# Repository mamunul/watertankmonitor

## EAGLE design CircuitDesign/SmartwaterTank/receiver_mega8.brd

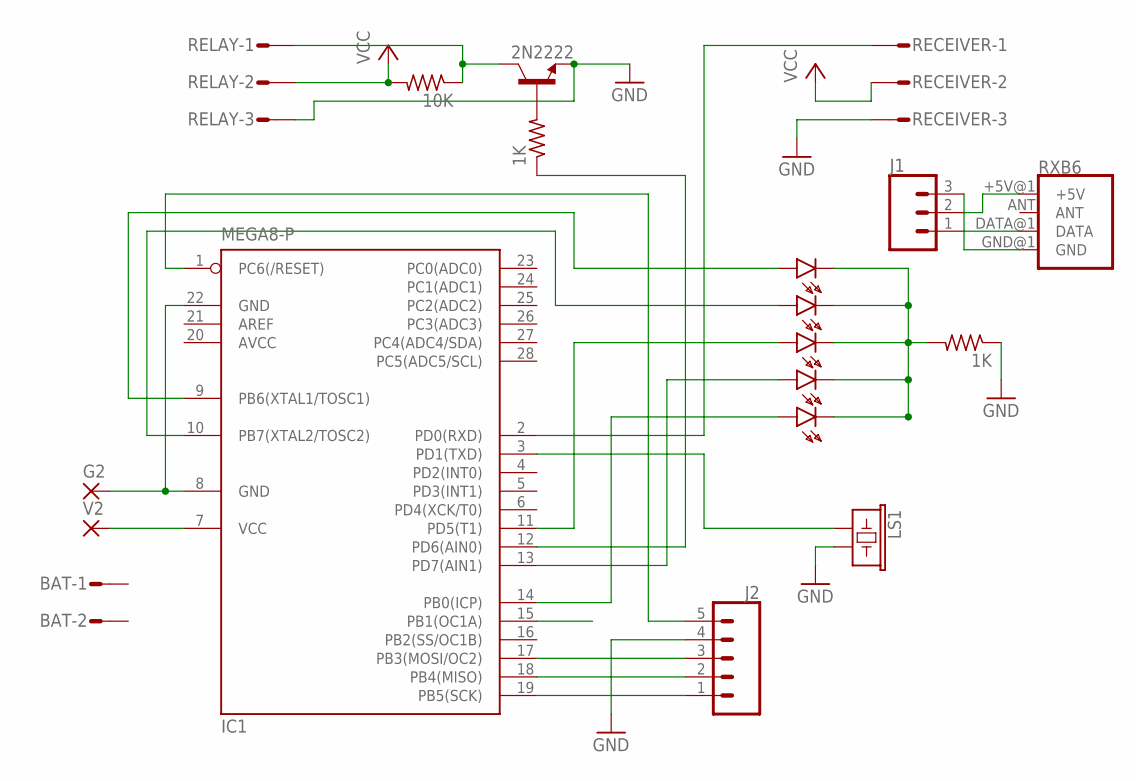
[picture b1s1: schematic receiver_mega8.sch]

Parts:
BAT: S02P
D2, D3, D4, D5, D6: HLMP6
G2: 1,6/0,8
IC1: MEGA8-P; DIL28-3
J1: CONN_03; 1X03
J2: CONN_05; 1X05
LS1: BUZZER-PTH_KIT; BUZZER-12MM-KIT
R1, R2: 1K; 0207/12
R5: 10K; 0207/12
RECEIVER: S03P
RELAY: S03P
RXB6: RF-LINK_RX
T1: 2N2222; TO92-CBE
V2: 1,6/0,8

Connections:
AVCC: IC1.20 (AVCC)
GND: J2.4, LS1.- (2), R2.1, RECEIVER.3, RELAY.3, T1.E
unnamed: R1.2, T1.B
unnamed: IC1.12 (PD6(AIN0)), R1.1
unnamed: J1.1, RXB6.DATA@1 (DATA)
unnamed: IC1.2 (PD0(RXD)), RECEIVER.1
unnamed: IC1.3 (PD1(TXD)), LS1.+ (1)
unnamed: D2.K, D3.K, D4.K, D5.K, D6.K, R2.2
unnamed: G2.1, IC1.8 (GND), IC1.22 (GND)
unnamed: IC1.7 (VCC), V2.1
unnamed: J1.3, RXB6.GND@1 (GND)
unnamed: D6.A, IC1.9 (PB6(XTAL1/TOSC1))
unnamed: D5.A, IC1.10 (PB7(XTAL2/TOSC2))
unnamed: D4.A, IC1.11 (PD5(T1))
unnamed: D3.A, IC1.13 (PD7(AIN1))
unnamed: J1.2, RXB6.+5V@1 (+5V)
unnamed: D2.A, IC1.14 (PB0(ICP))
unnamed: R5.1, RELAY.1, T1.C
unnamed: IC1.19 (PB5(SCK)), J2.1
unnamed: IC1.18 (PB4(MISO)), J2.2
unnamed: IC1.17 (PB3(MOSI/OC2)), J2.3
unnamed: IC1.1 (PC6(/RESET)), J2.5
VCC: R5.2, RECEIVER.2, RELAY.2

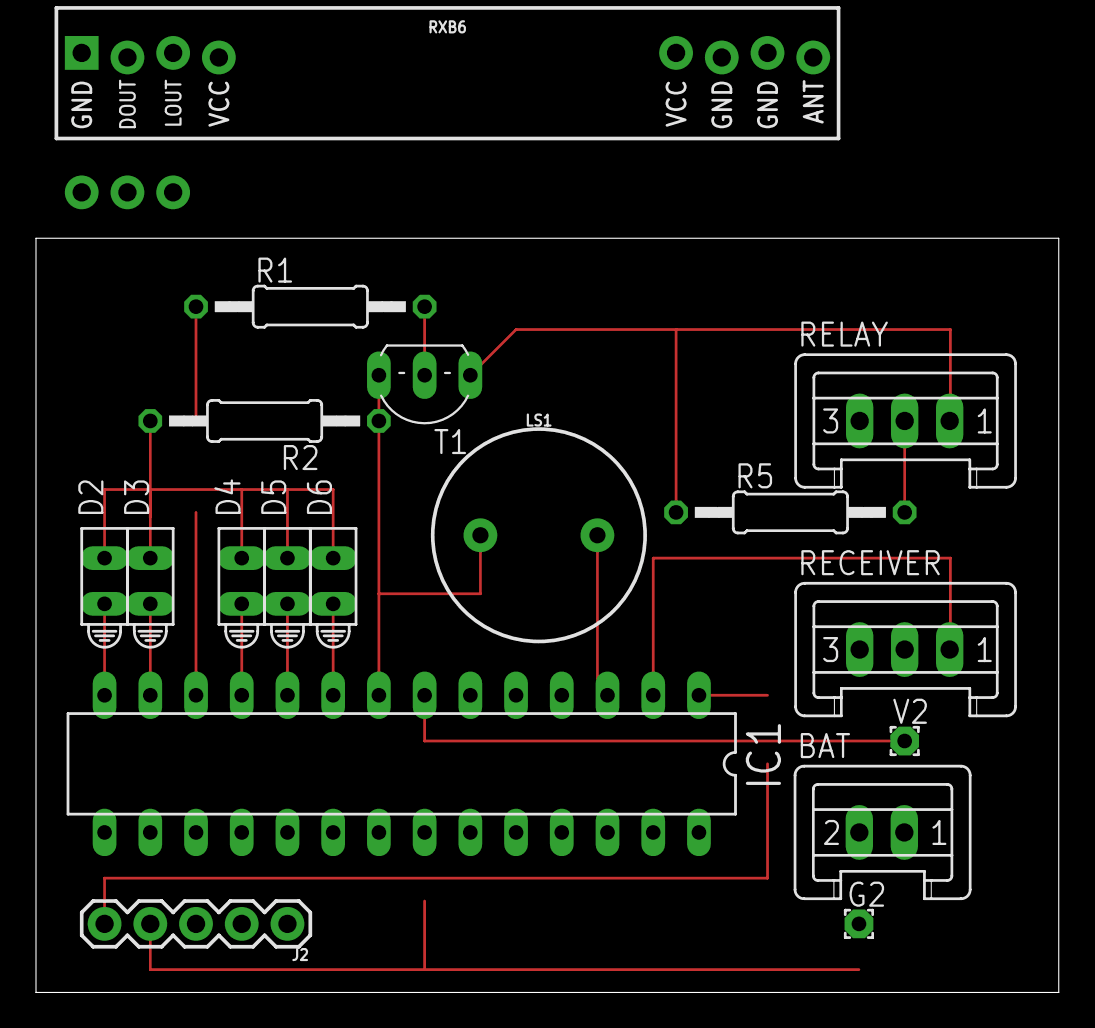
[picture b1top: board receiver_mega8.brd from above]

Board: 2 copper layers, 56.8 x 41.9 mm, 19 parts (1 on the bottom side), 22 nets.

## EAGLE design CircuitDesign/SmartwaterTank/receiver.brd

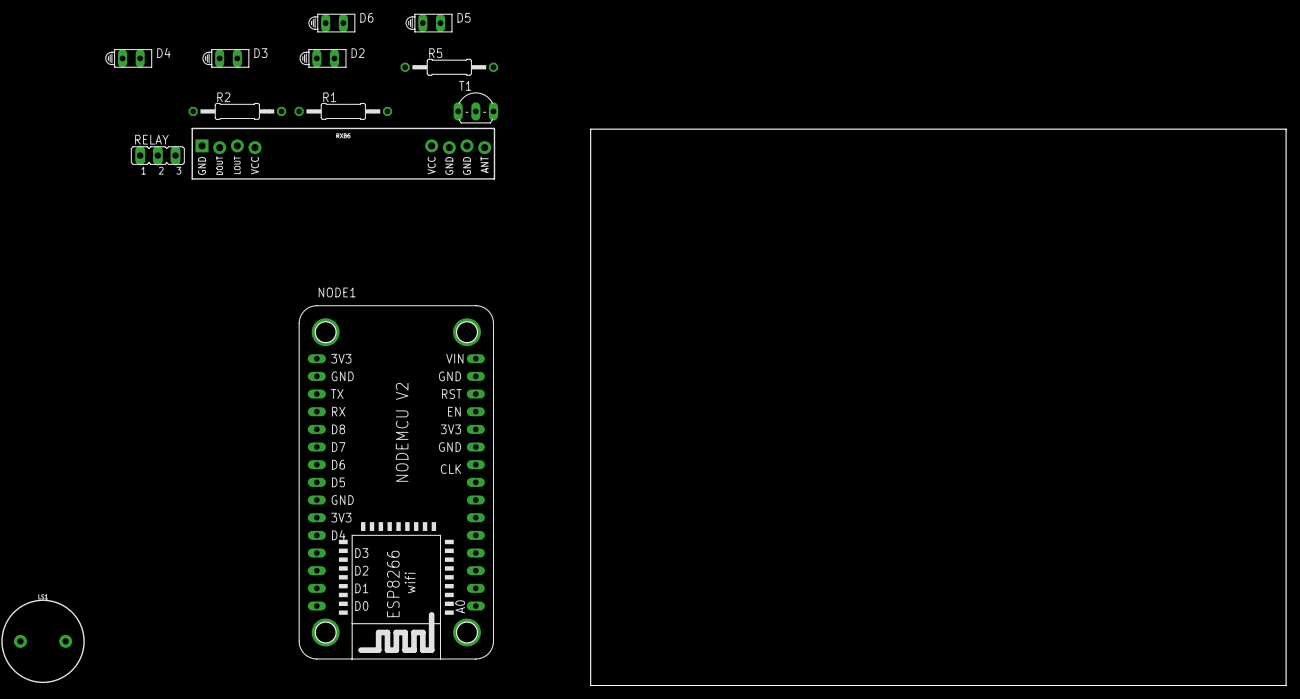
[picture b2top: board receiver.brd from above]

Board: 2 copper layers, 100.0 x 80.0 mm, 13 parts (0 on the bottom side), 14 nets, no tracks yet.

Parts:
D2, D3, D4, D5, D6: HLMP6
LS1: BUZZER-PTH_KIT; BUZZER-12MM-KIT
NODE1: NODEMCU_ESP8266
R1, R2: 1K; 0207/12
R5: 10K; 0207/12
RELAY: JP2
RXB6: RF-LINK_RX
T1: 2N2222; TO92-CBE

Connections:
3V3: NODE1.3V3@1, NODE1.3V3@2, NODE1.3V3@3
GND: LS1.-, NODE1.GND@1, NODE1.GND@2, NODE1.GND@3, NODE1.GND@4, R2.1, RELAY.3, RXB6.GND@1, T1.E
unnamed: R1.2, T1.B
unnamed: NODE1.D0, R1.1
unnamed: R5.1, RELAY.2, T1.C
unnamed: NODE1.D4, RXB6.DATA@1
unnamed: LS1.+, NODE1.D1
unnamed: D2.K, D3.K, D4.K, D5.K, D6.K, R2.2
unnamed: D6.A, NODE1.D8
unnamed: D5.A, NODE1.D7
unnamed: D4.A, NODE1.D6
unnamed: D3.A, NODE1.D5
unnamed: D2.A, NODE1.D3
VCC: R5.2, RELAY.1, RXB6.+5V@1

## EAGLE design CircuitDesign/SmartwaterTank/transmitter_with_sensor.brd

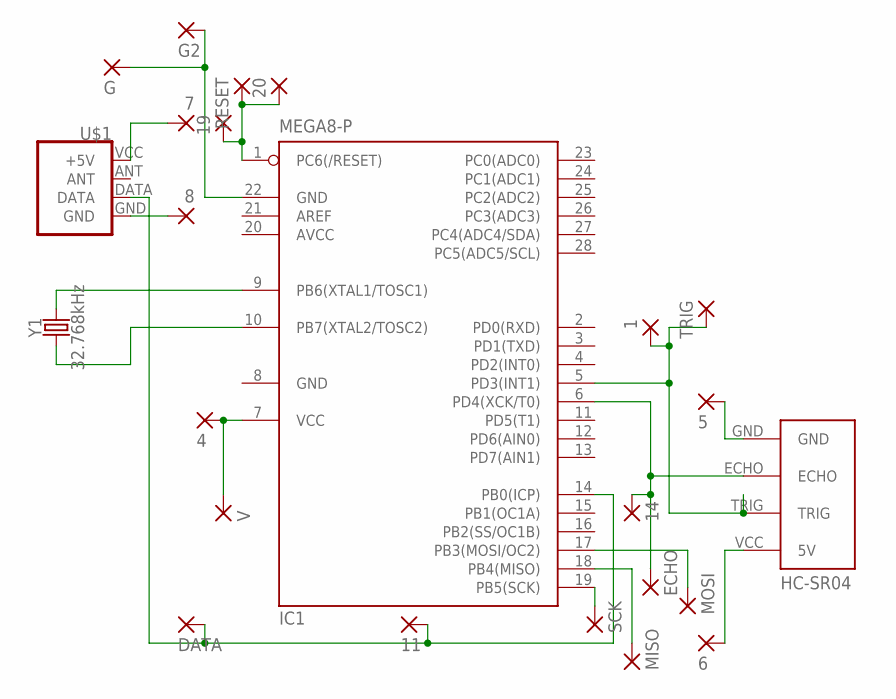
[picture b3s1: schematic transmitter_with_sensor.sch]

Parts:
1, 4, 5, 6, 7, 8, 11, 14, 19, 20: WIREPAD1,6/0,8; 1,6/0,8
DATA: WIREPAD1,6/0,8; 1,6/0,8
ECHO: WIREPAD1,6/0,8; 1,6/0,8
G, G2: WIREPAD1,6/0,8; 1,6/0,8
IC1: MEGA8-P; DIL28-3
J_ULTRASONIC_1: HC-SR04; HC-SR04_FOOTPRINT
MISO: WIREPAD1,6/0,8; 1,6/0,8
MOSI: WIREPAD1,6/0,8; 1,6/0,8
RESET: WIREPAD1,6/0,8; 1,6/0,8
SCK: WIREPAD1,6/0,8; 1,6/0,8
TRIG: WIREPAD1,6/0,8; 1,6/0,8
U$1: RF-LINK_TX
V: WIREPAD1,6/0,8; 1,6/0,8
Y1: 32.768kHz; CRYSTAL-PTH-2X6-CYL

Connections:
AVCC: IC1.20 (AVCC)
GND: IC1.8 (GND)
unnamed: 6.1, J_ULTRASONIC_1.VCC (5V)
unnamed: G.1, G2.1, IC1.22 (GND)
unnamed: 4.1, IC1.7 (VCC), V.1
unnamed: 5.1, J_ULTRASONIC_1.GND
unnamed: 8.1, U$1.GND
unnamed: 7.1, U$1.VCC (+5V)
unnamed: IC1.9 (PB6(XTAL1/TOSC1)), Y1.2
unnamed: IC1.10 (PB7(XTAL2/TOSC2)), Y1.1
unnamed: 19.1, 20.1, IC1.1 (PC6(/RESET)), RESET.1
unnamed: 14.1, ECHO.1, IC1.6 (PD4(XCK/T0)), J_ULTRASONIC_1.ECHO
unnamed: 1.1, IC1.5 (PD3(INT1)), J_ULTRASONIC_1.TRIG, TRIG.1
unnamed: IC1.17 (PB3(MOSI/OC2)), MOSI.1
unnamed: IC1.18 (PB4(MISO)), MISO.1
unnamed: 11.1, DATA.1, IC1.14 (PB0(ICP)), U$1.DATA
unnamed: IC1.19 (PB5(SCK)), SCK.1

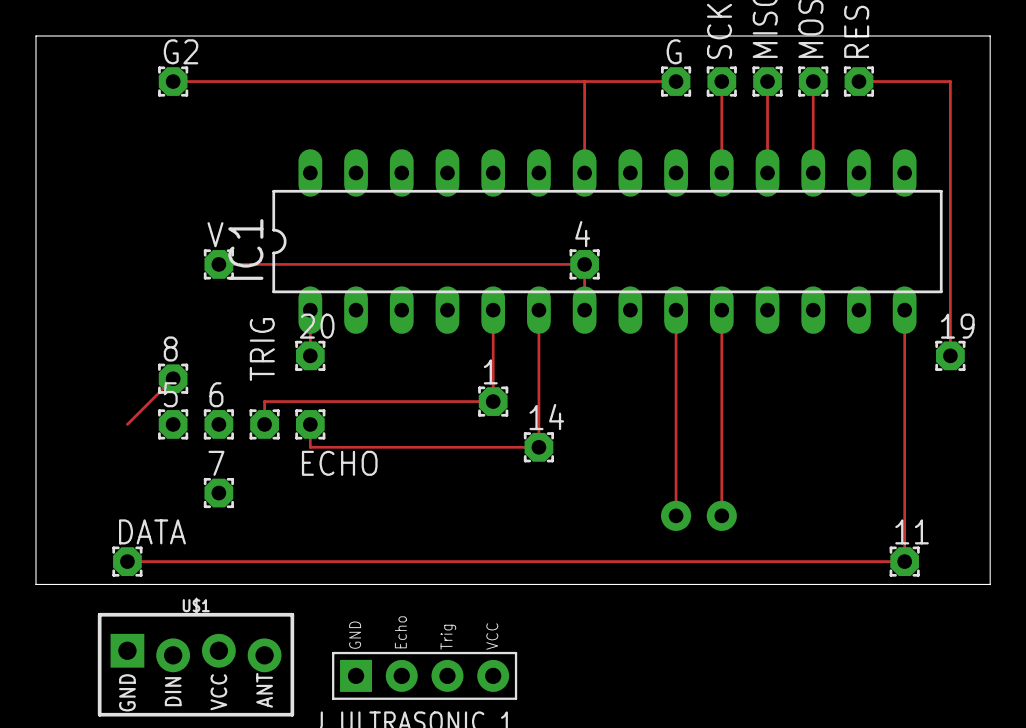
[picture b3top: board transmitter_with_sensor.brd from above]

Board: 2 copper layers, 53.0 x 30.5 mm, 24 parts (1 on the bottom side), 15 nets.

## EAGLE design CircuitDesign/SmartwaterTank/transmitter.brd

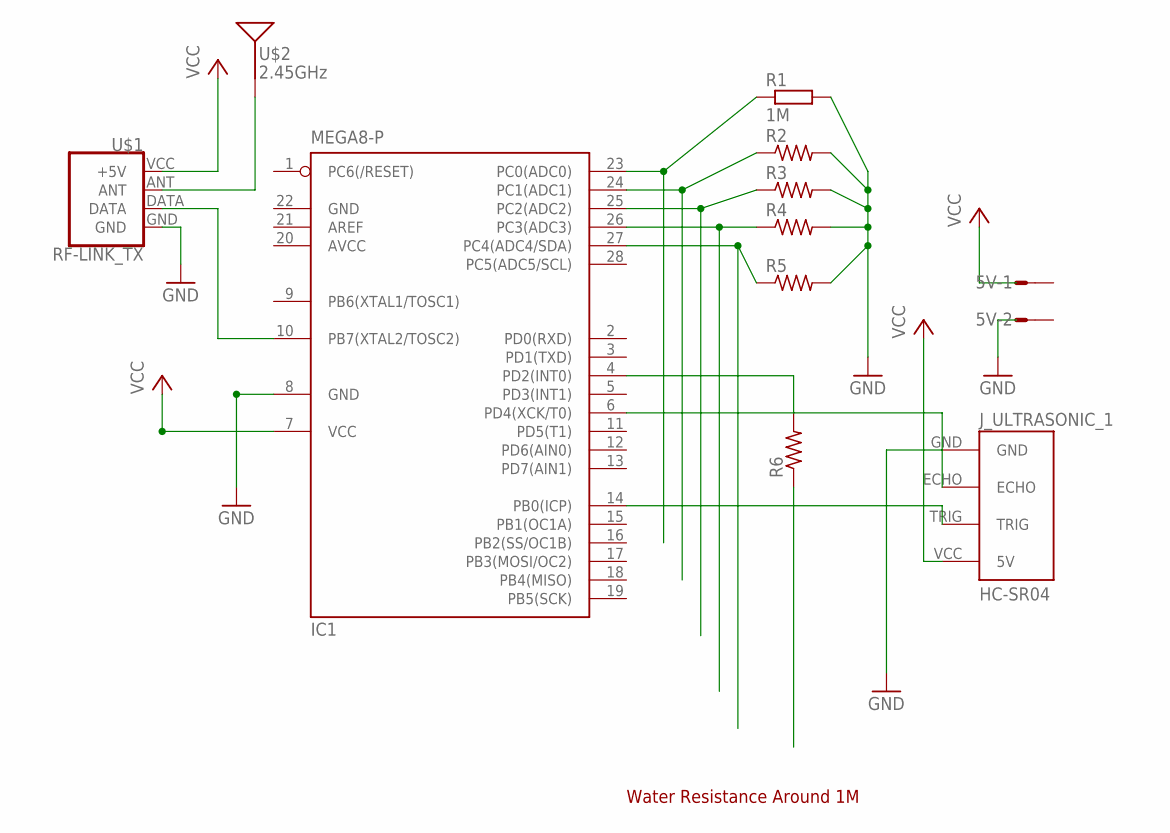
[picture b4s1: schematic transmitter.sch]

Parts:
5V: S02P
IC1: MEGA8-P; DIL28-3
J_ULTRASONIC_1: HC-SR04; HC-SR04_FOOTPRINT
R1: 1M; 0204/7
R2, R3, R4, R5, R6: R-US_0204/2V; 0204V
U$1: RF-LINK_TX
U$2: 2.45GHz; ANT-2.4GHZ-6.5X2.2MM

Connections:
AVCC: IC1.20 (AVCC)
GND: IC1.8 (GND), IC1.22 (GND), J_ULTRASONIC_1.GND, R1.2, R2.2, R3.2, R4.2, R5.2, U$1.GND
unnamed: IC1.23 (PC0(ADC0)), R1.1
unnamed: IC1.26 (PC3(ADC3)), R4.1
unnamed: IC1.25 (PC2(ADC2)), R3.1
unnamed: IC1.24 (PC1(ADC1)), R2.1
unnamed: IC1.27 (PC4(ADC4/SDA)), R5.1
unnamed: IC1.10 (PB7(XTAL2/TOSC2)), U$1.DATA
unnamed: U$1.ANT, U$2.FEED
unnamed: IC1.4 (PD2(INT0)), R6.2
unnamed: IC1.6 (PD4(XCK/T0)), J_ULTRASONIC_1.ECHO
unnamed: IC1.14 (PB0(ICP)), J_ULTRASONIC_1.TRIG
VCC: IC1.7 (VCC), J_ULTRASONIC_1.VCC (5V), U$1.VCC (+5V)

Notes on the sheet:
Water Resistance Around 1M

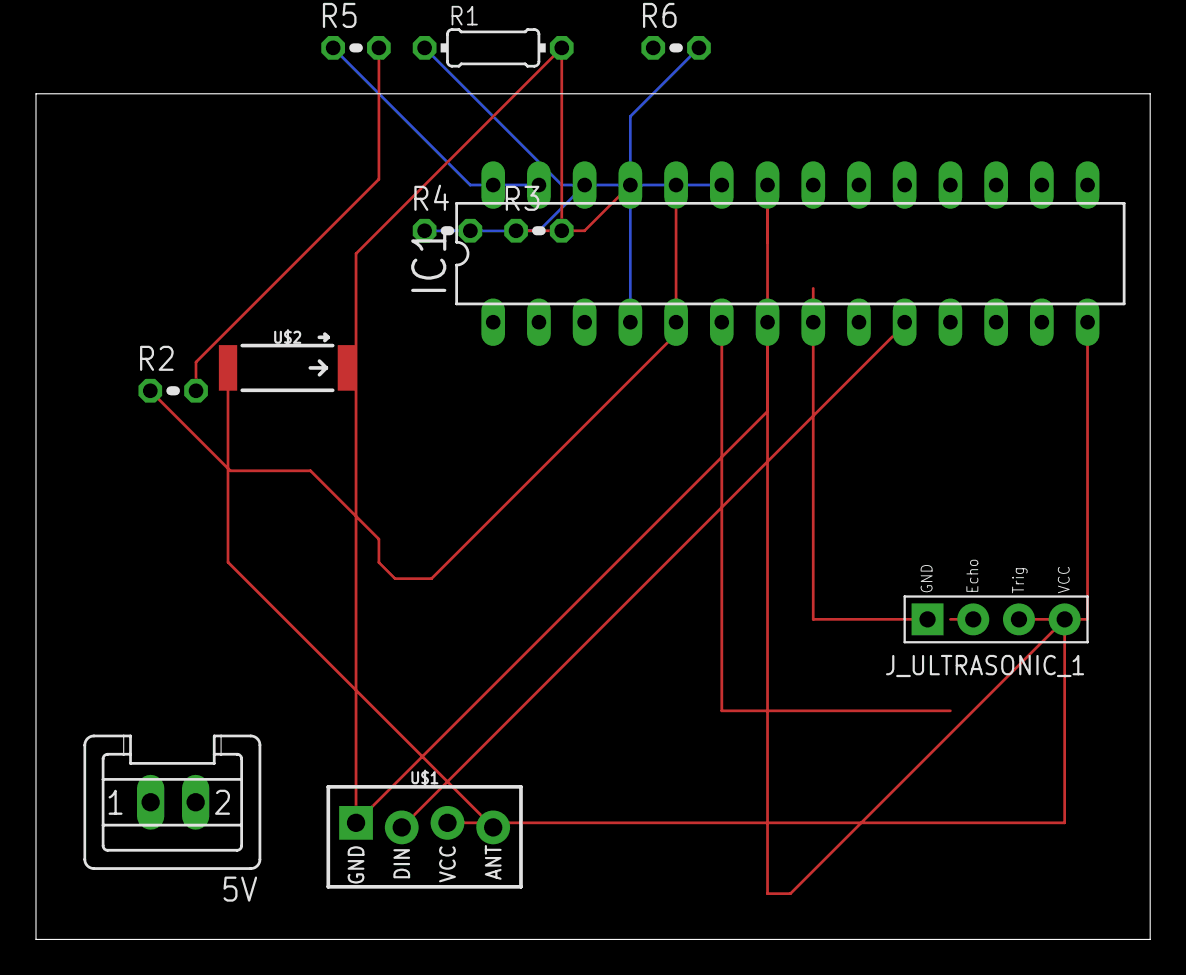
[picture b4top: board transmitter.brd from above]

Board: 2 copper layers, 11 parts (0 on the bottom side), 12 nets.

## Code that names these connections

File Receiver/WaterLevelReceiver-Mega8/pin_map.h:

int level1 = PIN_PD0;
int level2 = PIN_PD1;
int level3 = PIN_PD2;
int level4 = PIN_PD3;
int level5 = PIN_PD4;

int ReceivePIN = PIN_PD5;
int switchRelay = PIN_PD6;
int buzzerPin = PIN_PD7;  //GPIO_ID_PIN(1);

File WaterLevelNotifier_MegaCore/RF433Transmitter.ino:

// #include <RH_ASK.h>
// #include <SPI.h>
// RH_ASK driver(2000, PIN_PB6, PIN_PB7, PIN_PD5);  //rx,tx
RCSwitch mySwitch = RCSwitch();
void rf_setup() {
  // driver.init();
  // Transmitter is connected to Arduino Pin #10
  mySwitch.enableTransmit(PIN_PB0);

  // Optional set protocol (default is 1, will work for most outlets)
  // mySwitch.setProtocol(2);

  // Optional set pulse length.
  // mySwitch.setPulseLength(320);

  // Optional set number of transmission repetitions.
  // mySwitch.setRepeatTransmit(15);
}

void rf_send(long message) {
  mySwitch.send(message, 16);
  delay(100);
  // driver.send((uint8_t *)message, strlen(message));
  // driver.waitPacketSent();
}

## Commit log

2022-08-02 tested and working code
2022-08-02 remove unused code
2022-08-02 add status in transmitter
2022-08-02 create a new file for rf433 module code
2022-08-03 refactpr transmitter code
2022-08-03 add serial output in avr
2022-08-03 rename pin no
2022-08-07 implement rf24l01
2022-08-08 add analog comparator
2022-08-08 add homebridge test code
2022-08-09 connect esp with mqtt
2022-08-10 subscribe a topic
2022-08-10 refactor topic names
2022-08-13 read water levels
2022-08-13 send tank level data through rf to receiver
2022-08-14 receive water tank levels and toggle relay switch
2022-08-28 add buzzer and relay operation when the water motor switches
2022-08-29 add design files
2022-08-30 sync mqtt receive with transmitter data
2022-09-01 add distance sensor in transmitter
2022-09-01 change rf library to reduce code size
2022-09-03 add wifi manager file
2022-09-03 register wifi accesspoint
2022-09-03 remove wifi reseting on every startup of the chip
2022-09-23 implement distance sensor in water level detection
2022-10-11 Issue #1: add sleep mode in transmitter
2022-10-11 Issue #5: add sleep in receiver, not tested
2022-10-17 Issue #5: receive long from transmitter as value exceeds int8
2022-10-18 Issue #5: update transmitter schema
2022-11-06 Issue #2: complete transmitter board design for vero board
2022-11-06 Issue #2: remove unnecessary texts from schematic
2022-12-31 Issue #1: fix sleep issue - using 32K crystal provides 15s sleep time tested in breadboard
2022-12-31 Issue #2: update pcb design
2022-12-31 Issue #2: update schema and board
2023-01-02 Issue #6: add receiver schema for atmega8
2023-01-02 Issue #6: refactor receiver code
2023-01-03 Issue #6: add receiver code for atmega8
2023-01-06 Issue #6: update receiver board for vero board

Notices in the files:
parts and their libraries:
SparkFun-RF: Licensing: Creative Commons ShareAlike 4.0 International - https://creativecommons.org/licenses/by-sa/4.0
